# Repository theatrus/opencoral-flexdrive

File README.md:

# OpenCoral FlexDrive High Current LED Driver

LM3404(HV) based dual LED driver with optional MCU supervision / dimming
support.

# Features

 * Dual LM3404HV drivers and all power switching circuitry.
 * Runs on up to 60V input, 24-48VDC suggested.
 * Up to 1.5A per LED chain
 * On board MCU and power supply for dimming control of each channel
   (ATmega8)
 * RS485 transceiver and two RJ-12 jacks for control signals from a
   controller.
 * MCU is optional, dimming control can be done via external pins (PWM)

# License

CC-SA-NC 3.0.

See LICENSE.txt

# Design Status

This design was built and is in operation.

## Boards

Available on OSHPark:
http://oshpark.com/shared_projects/ymYU4l9N

# Files available

The original design is available as Eagle 6.x (XML-based) design
files, in the eagle/ directory.

Gerber files from the Eagle board file are made available in the
gerber/ directory.

Schematic PDF is available in the root of this repository.

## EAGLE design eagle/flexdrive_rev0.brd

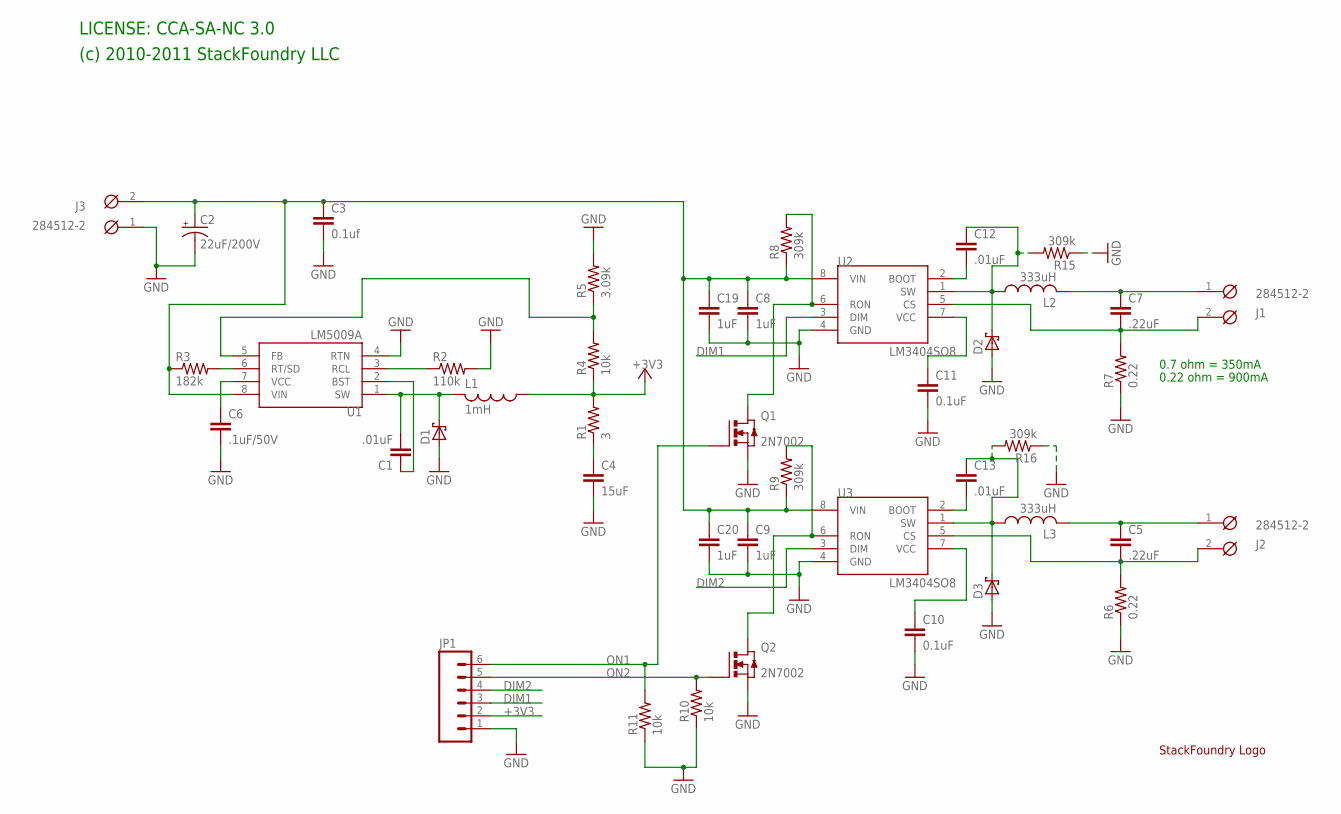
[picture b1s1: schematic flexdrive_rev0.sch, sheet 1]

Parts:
C1: .01uF; C0603
C2: 22uF/200V; E5-10,5
C3: 0.1uf; C0805
C4: 15uF; CT7343
C5, C7: .22uF; C1206
C6: .1uF/50V; C1206
C8, C9, C19, C20: 1uF; C1206
C10, C11: 0.1uF; C1206
C12, C13: .01uF; C1206
D1, D2, D3: SCHOTTKY-DIODESMA; SMA
J1, J2, J3: 284512-2
JP1: M06SIP; 1X06
L1: 1mH; MSS1246
L2, L3: 333uH; DO5040H
LOGO1: SFLOGO
Q1, Q2: 2N7002; SOT23
R1: 3; R0603
R2: 110k; R0603
R3: 182k; R0603
R4, R10, R11: 10k; R0603
R5: 3.09k; R0603
R6, R7: 0.22; R1206
R8, R9, R15, R16: 309k; R0805
U1: LM5009A; MSOP-8
U2, U3: LM3404SO8; SO08

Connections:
+3V3: JP1.2, L1.1, R1.2, R4.1; also elsewhere on the board
DIM1: JP1.3, U2.3 (DIM); also elsewhere on the board
DIM2: JP1.4, U3.3 (DIM); also elsewhere on the board
GND: C2.-, C3.2, C4.- (2), C6.2, C8.2, C9.2, C10.2, C11.2, C19.2, C20.2, D1.A, D2.A, D3.A, J3.1, JP1.1, Q1.2 (S), Q2.2 (S), R2.2, R5.2, R6.1, R7.1, R10.1, R11.1, R15.1, R16.1, U1.4 (RTN), U2.4 (GND), U3.4 (GND); also elsewhere on the board
unnamed: C2.+, C3.1, C8.1, C9.1, C19.1, C20.1, J3.2, R3.1, R8.1, R9.1, U1.8 (VIN), U2.8 (VIN), U3.8 (VIN)
unnamed: C1.2, D1.C, L1.2, U1.1 (SW)
unnamed: C1.1, U1.2 (BST)
unnamed: C4.+ (1), R1.1
unnamed: R2.1, U1.3 (RCL)
unnamed: R3.2, U1.6 (RT/SD)
unnamed: C6.1, U1.7 (VCC)
unnamed: R4.2, R5.1, U1.5 (FB)
unnamed: C12.1, D2.C, L2.P$1 (1), R15.2, U2.1 (SW)
unnamed: C13.1, D3.C, L3.P$1 (1), R16.2, U3.1 (SW)
unnamed: C7.1, J1.1, L2.P$2 (2)
unnamed: C5.1, J2.1, L3.P$2 (2)
unnamed: C7.2, J1.2, R7.2, U2.5 (CS)
unnamed: C10.1, U3.7 (VCC)
unnamed: C11.1, U2.7 (VCC)
unnamed: C13.2, U3.2 (BOOT)
unnamed: C12.2, U2.2 (BOOT)
unnamed: C5.2, J2.2, R6.2, U3.5 (CS)
unnamed: Q1.3 (D), R8.2, U2.6 (RON)
unnamed: Q2.3 (D), R9.2, U3.6 (RON)
ON1: JP1.6, Q1.1 (G), R11.2; also elsewhere on the board
ON2: JP1.5, Q2.1 (G), R10.2; also elsewhere on the board

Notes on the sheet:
0.7 ohm = 350mA
0.22 ohm = 900mA
LICENSE: CCA-SA-NC 3.0
(c) 2010-2011 StackFoundry LLC

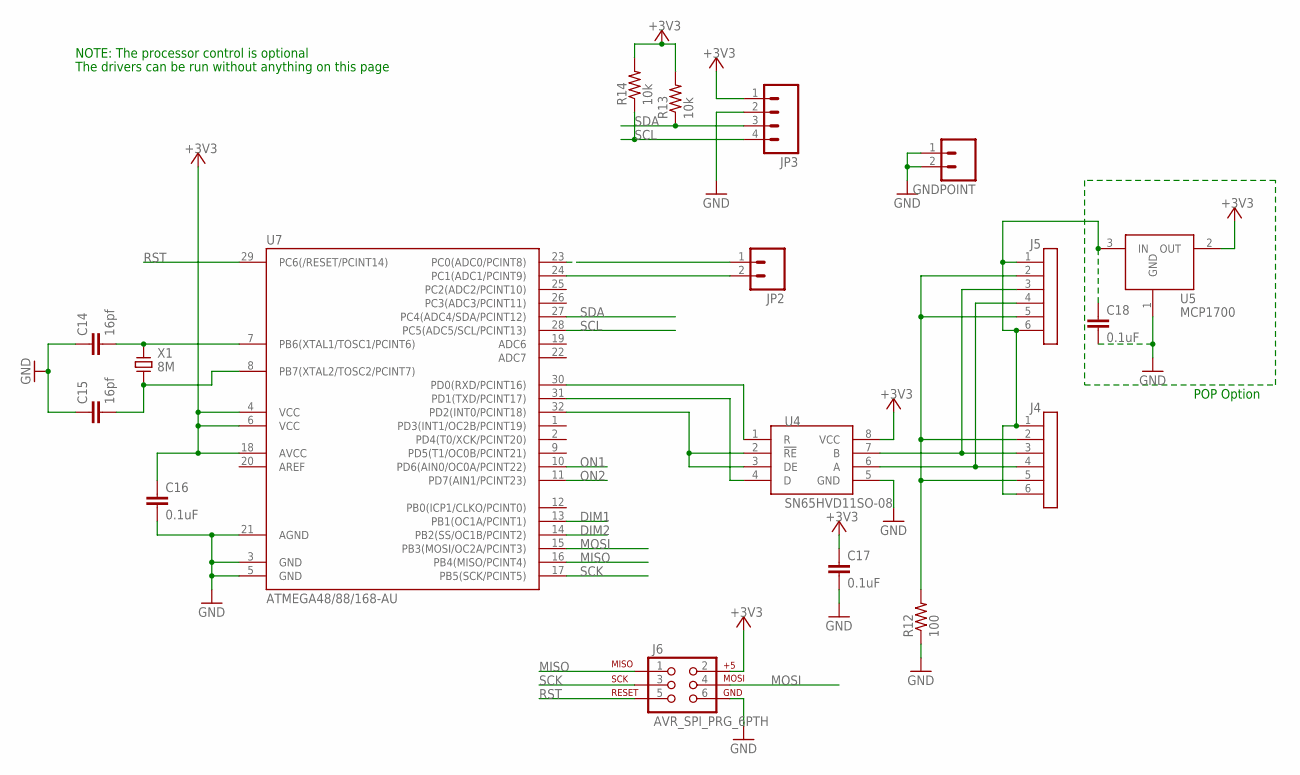
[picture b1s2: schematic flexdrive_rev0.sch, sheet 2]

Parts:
C14, C15: 16pf; C0603
C16, C17, C18: 0.1uF; C0603
GNDPOINT: M02PTH; 1X02
J4, J5: RJ12; A-2004-RJ12
J6: AVR_SPI_PRG_6PTH; 2X3
JP2: M02PTH; 1X02
JP3: M04PTH; 1X04
R12: 100; R0603
R13, R14: 10k; R0603
U4: SN65HVD11SO-08; SO-08
U5: MCP1700; SOT23
U7: ATMEGA48/88/168-AU; TQFP32-08
X1: 8M; HCM49

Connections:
+3V3: C16.1, C17.1, J6.2, JP3.1, R13.2, R14.2, U4.8 (VCC), U5.2 (OUT), U7.4 (VCC), U7.6 (VCC), U7.18 (AVCC); also elsewhere on the board
DIM1: U7.13 (PB1(OC1A/PCINT1)); also elsewhere on the board
DIM2: U7.14 (PB2(SS/OC1B/PCINT2)); also elsewhere on the board
GND: C14.1, C15.1, C16.2, C17.2, C18.2, GNDPOINT.1, GNDPOINT.2, J6.6, JP3.2, R12.1, U4.5 (GND), U5.1 (GND), U7.3 (GND), U7.5 (GND), U7.21 (AGND); also elsewhere on the board
MISO: J6.1, U7.16 (PB4(MISO/PCINT4))
MOSI: J6.4, U7.15 (PB3(MOSI/OC2A/PCINT3))
unnamed: U4.2 (!RE), U4.3 (DE), U7.32 (PD2(INT0/PCINT18))
unnamed: C14.2, U7.7 (PB6(XTAL1/TOSC1/PCINT6)), X1.P$1
unnamed: C15.2, U7.8 (PB7(XTAL2/TOSC2/PCINT7)), X1.P$2
unnamed: U4.1 (R), U7.30 (PD0(RXD/PCINT16))
unnamed: U4.4 (D), U7.31 (PD1(TXD/PCINT17))
unnamed: J4.3, J5.3, U4.7 (B)
unnamed: J4.4, J5.4, U4.6 (A)
unnamed: J4.2, J4.5, J5.2, J5.5, R12.2
unnamed: C18.1, J4.1, J4.6, J5.1, J5.6, U5.3 (IN)
unnamed: JP2.1, U7.23 (PC0(ADC0/PCINT8))
unnamed: JP2.2, U7.24 (PC1(ADC1/PCINT9))
ON1: U7.10 (PD6(AIN0/OC0A/PCINT22)); also elsewhere on the board
ON2: U7.11 (PD7(AIN1/PCINT23)); also elsewhere on the board
RST: J6.5, U7.29 (PC6(/RESET/PCINT14))
SCK: J6.3, U7.17 (PB5(SCK/PCINT5))
SCL: JP3.4, R14.1, U7.28 (PC5(ADC5/SCL/PCINT13))
SDA: JP3.3, R13.1, U7.27 (PC4(ADC4/SDA/PCINT12))

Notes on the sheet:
POP Option
NOTE: The processor control is optional
The drivers can be run without anything on this page

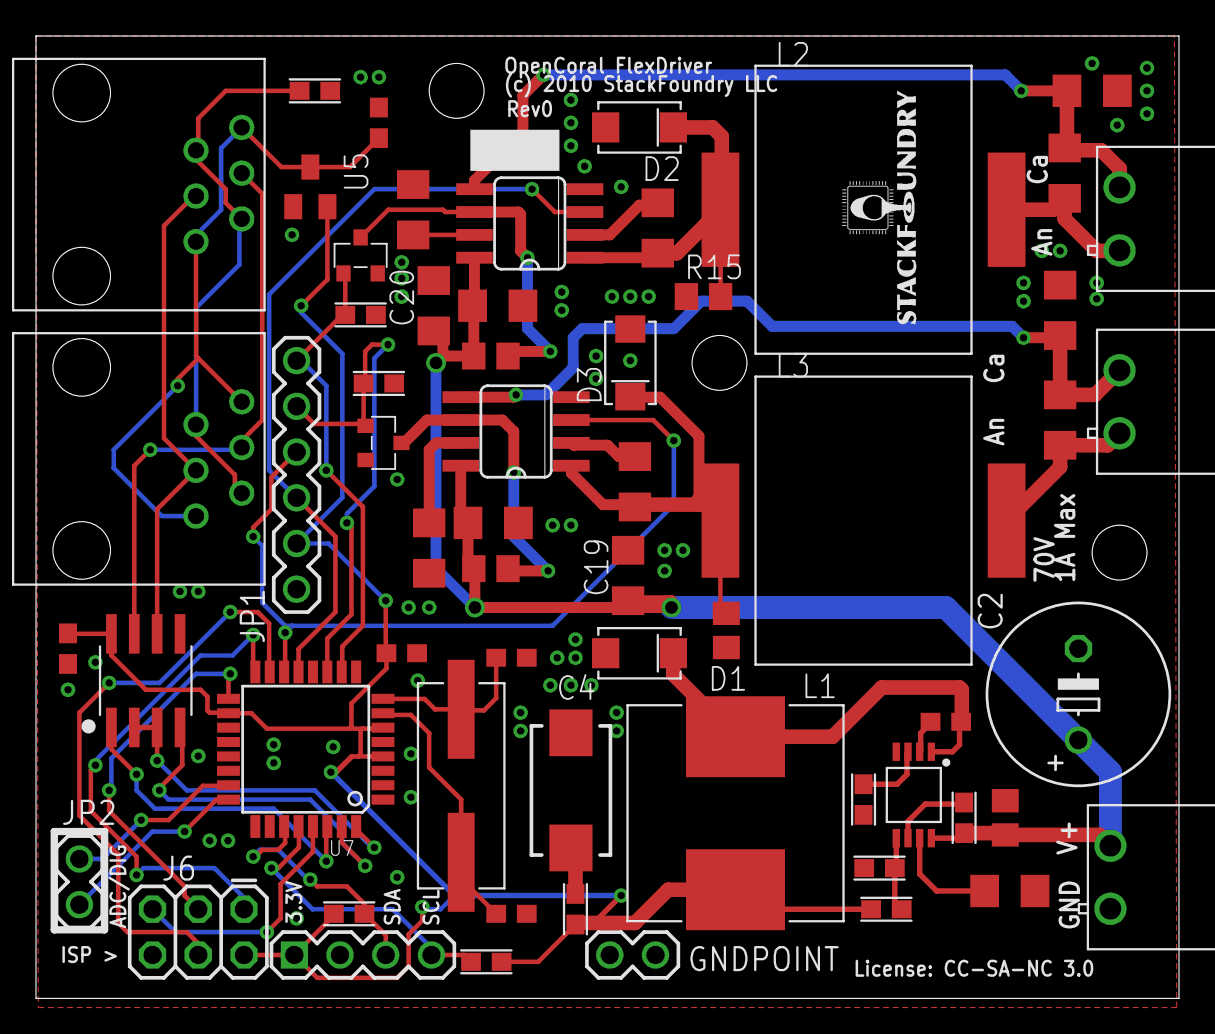
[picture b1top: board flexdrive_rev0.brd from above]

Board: 2 copper layers, 63.5 x 53.5 mm, 62 parts (0 on the bottom side), 43 nets.

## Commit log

2014-04-11 OpenCoral FlexDrive
2014-04-11 Add BOM
2014-04-11 Readme

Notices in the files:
eagle/flexdrive_rev0.brd:
(c) 2010 StackFoundry LLC
